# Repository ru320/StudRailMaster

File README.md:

<p align="center"><b>Drive your brick-built trains from your computer or a home-made remote –<br>via Bluetooth, without internet, without an account.</b></p>

<p align="center">🇩🇪 <a href="README.de.md">Deutsche Fassung</a> · <a href="docs/en/install.md">Installation</a> · <a href="docs/en/user-guide.md">User guide</a> · <a href="docs/en/remote-setup.md">Remote</a></p>

---

## Why?

The layout runs trains with motor hubs from three makers: a cheap JMC hub, a Mould King 4.0 from the Orient Express and a LEGO City Hub from the freight train 60337. Every hub wants its own phone app. Every app has different sliders, and driving two trains at once means two phones.

I wanted **one control desk for all trains** – ideally with **real levers** you push with your thumb, and a **big red button** that really stops everything. No account, no ads, no cloud. That turned into two things:

| | |
|---|---|
| **Stud Rail Master** – the PC program | for Windows, macOS and Linux. Find hubs, add photos of your trains, assign levers, drive. Needs no extra hardware. |
| **Stud Rail Master Quadro** – the remote | an ESP32 with four slide pots, direction switches and an emergency stop. Drives up to four hubs on its own, no PC needed; set up through a web page in your phone's browser. |

Both share the same drivers and take turns: when the PC starts it takes over the radio, when it quits the remote drives again.

## What it looks like

Every socket of every hub gets a throttle – spread any way you like: two motors on one throttle, one throttle across several hubs (even from different makers), single motors inverted. More in the [user guide](docs/en/user-guide.md#the-idea-throttles-and-hubs).

- **One lever per throttle** – drag up to go faster, one tap to change direction, a big red emergency stop (also on the space bar).
- **Your trains, your pictures** – put a photo on every hub so you always know which lever moves which train.
- **Many trains at once** – up to 16 throttles; one throttle can drive several locomotives, even from different makers.
- **Gentle direction changes** – the train slows down and starts off the other way, instead of jerking.
- **Stays at home** – no internet, no account, no advertising, no data collection.
- **Help built in** – the same guide as here, offline in the program (the **?** button).

## Which hubs?

| Hub | Windows | macOS | Linux | Remote |
|---|:-:|:-:|:-:|:-:|
| **JMC hub** (shows up as “JG_JMC-…”, ports A–D) | ✔ | ✔ | ✔ | ✔ |
| **Mould King 4.0** (ports A–D, up to 3 hubs) | ⚠ not yet tested | ✘ → Linux or ESP32 with web page | ✔ one-time unlock | ✔ |
| **LEGO Powered Up City Hub** (88009, e.g. set 60337, ports A/B) | ✔ | ✔ | ✔ | ✔ |

**Planned:**
- **IR hubs** (infrared, protocol like LEGO Power Functions) – transmitter in the remote, the window in the case is already there
- **BlueBrixx hubs with 2.4 GHz radio**
- **LEGO Technic Hub** (4 ports), **Mould King 6.0** (as soon as the hubs are available)

## Get started

1. Download the program for your system from the **releases** page and unpack it.
2. Start it, switch your hub on, find it under *Settings → Find hubs*, assign a throttle – and off you go.

Step by step: **[Installation](docs/en/install.md)** · **[User guide](docs/en/user-guide.md)** · **[Set up the remote](docs/en/remote-setup.md)** · **[Together with the remote](docs/en/esp-sync.md)**

Want to try it without a hub first? **Demo mode** simulates three trains (see the user guide).

<details>
<summary><b>Or run it from source</b></summary>

With Python 3.10 or newer: download or clone this repository, then start `app/start.sh` (Linux), `app/start.command` (macOS) or `app/start.bat` (Windows). The first start sets everything up and downloads the required Python packages once; after that it starts right away.
</details>

## Safety

Some hubs simply keep running their last command when they hear nothing more. So everywhere:

- **Emergency stop** halts every train immediately – even in the middle of a direction change.
- **Nothing moves until every lever has been at 0** – after switching on and after every emergency stop.
- **On quit, on a lost connection and before every restart** a stop is sent actively.
- When you drive through the remote's web page, it triggers an emergency stop as soon as the page has been silent for 2 seconds.

## The long road

No maker has published its protocol (except LEGO). What now fits into a few lines of driver cost quite a few evenings:

<details>
<summary><b>JMC: the hub that would not listen</b></summary>

The protocol comes from a capture of the original app: 11 bytes, a checksum, done – or so I thought. The hub still ignored every drive command. The reason: a freshly switched-on hub has to receive a **stop** first, before it moves at all. Then came the second surprise: it has **no watchdog**. If the connection drops, the motor just keeps running – more than 20 seconds in the test, until it was switched off. Since then every path out of the program actively sends stop. And because ports A+B share one speed byte, two motors stuttered as soon as you tried to drive them separately.
</details>

<details>
<summary><b>Mould King 4.0: radio without a connection</b></summary>

This hub never connects. It is controlled through encrypted **Bluetooth advertising packets** that the app sends every 100 ms with a changing address. The encryption could be rebuilt thanks to other people's work (see [THIRD_PARTY.md](THIRD_PARTY.md)) – and still nothing moved. In broadcast mode Linux drops three inconspicuous bytes (the “flags” `02 01 02`), and **without exactly those three bytes the hub ignores everything**. On Linux the commands now go straight to the Bluetooth chip. macOS doesn't allow that at all. By the way: one reference had forward and reverse swapped.
</details>

<details>
<summary><b>LEGO City Hub: the impatient one</b></summary>

The only hub with open documentation – and still fussy: if nobody connects right away, it **switches itself off after a few seconds**. So the program no longer searches at leisure but grabs it the moment it shows up.
</details>

<details>
<summary><b>Packaging: 301 MB for one window</b></summary>

The first Linux program accidentally bundled the whole GTK toolkit and weighed **301 MB** – and still didn't run everywhere, because WebKitGTK can't be packed portably. Now it ships Qt WebEngine (171 MB). The built-in Chromium sandbox failed on locked-down namespaces, an AppImage can't be given special privileges, and the Mould King radio needs exactly such a privilege – so there is now a tiny helper you unlock once with your password. And for a while, the browser opened every time along with the program window.
</details>

New findings about hubs go into `drivers/*.json` as test vectors – so PC and remote check on every build that they still send exactly the same bytes.

## The remote

An ESP32 DevKit, four 75 mm slide pots, four toggle switches with an LED for the direction, an emergency-stop button and 4× AA batteries in a printed case. The firmware also works on its own without any of that – then the levers are sliders on the web page `StudRailMasterQuadro.local`.

> **Preview – not yet printed or tested.** The case is fully designed on the computer but nobody has built it yet. If you print it first, feedback is welcome.

- **[Case](hardware/gehaeuse/README.md)** (German) – 180 × 180 mm desk, every part printable in one colour (build plate from 185 × 185 mm), STL files and a parametric CAD model (SolidCraft, STEP)
- **[Parts list](hardware/BOM.md)** (German) – electronics, bought parts, screws
- **[Flash and set up the firmware](docs/en/remote-setup.md)** – already works with a bare ESP32 DevKit
- Schematic to follow; the pin assignment is in the parts list.

## For developers

The project consists of the PC program (`app/`, Python) and the firmware of the ESP32 remote (`src/`, `lib/`, PlatformIO). Both share the same hub drivers (`drivers/`).

- [Drivers: shared between ESP32 and PC](docs/en/dev/drivers.md)
- [Building, testing, internals](docs/en/dev/building.md)

## License

Free software and open hardware – if you change it and pass it on, you must share it under the same terms:

| Part | License |
|---|---|
| Software (`app/`, `src/`, `lib/`, `test/`, `tools/`, `drivers/`) | [GPL-3.0-or-later](LICENSE) |
| Hardware (`hardware/`: schematic, PCB, enclosure) | [CERN-OHL-S-2.0](LICENSES/CERN-OHL-S-2.0.txt) |
| Docs, images, logo (`docs/`, `README*`) | [CC BY-SA 4.0](LICENSES/CC-BY-SA-4.0.txt) |

Third-party parts (Barlow fonts, prior work on Mould King) and their licenses: [THIRD_PARTY.md](THIRD_PARTY.md).

LEGO® is a trademark of the LEGO Group, Mould King a trademark of its manufacturer. This project is not sponsored or endorsed by either; the names only describe which hubs it works with.

---

<p align="center"><i>In Herbrechtingen ist es immer am schönsten!</i></p>

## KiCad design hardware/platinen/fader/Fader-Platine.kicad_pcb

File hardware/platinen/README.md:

# Platinen Handgerät „Stud Rail Master Quadro“

> **Entwurf, ungetestet.** Beide Platinen sind platziert und gegen das Gehäuse geprüft, aber noch nicht gefertigt. Vor der Bestellung die Punkte unter [Vor der Bestellung prüfen](#vor-der-bestellung-prüfen) abhaken.

Zwei Platinen, 2 Lagen, 1,6 mm FR4, Masse auf beiden Seiten als Fläche:

| Platine | Größe | Inhalt |
|---|---|---|
| [Fader-Platine](fader/) | 91 × 91 mm | 4 Schiebepotis B103 75 mm, je 1 k + 100 nF am Schleifer, Stecker zur Hauptplatine |
| [Hauptplatine](hauptplatine/) | 100 × 52 mm | ESP32-DevKit V1 (30 Pin, kopfüber darunter), MT3608-Modul (unten), 1N5819, Batteriemessung, IR-Treiber, LED-Widerstände, Stecker für alles am Gehäuse, Anschluss für ein 2,4-GHz-Funkmodul |

Je Platine liegen Schaltplan (`.kicad_sch`), Platine (`.kicad_pcb`) und Projekt (`.kicad_pro`) im Ordner. Eigene Footprints (Fader, MT3608-Modul) stehen in [`ZugFern.pretty/`](ZugFern.pretty/).

## Im Gehäuse

- **Fader-Platine:** Sie sitzt auf den 4 Säulen unter der Frontplatte (4 × M3 × 6 in Gewindeeinsätze). Die Fader drücken mit ihrer Oberseite gegen die Frontplatte. Der Stecker J1 sitzt **unten** auf der Platine.
- **Hauptplatine:** Sie liegt waagrecht im linken hinteren Teil der Unterschale, 12,4 mm über dem Boden, auf 4 eigenen Säulen (4 × M3 × 6 von oben).
  - Das ESP32-DevKit hängt kopfüber darunter: Seine Stiftleisten stecken von unten durch die Platine und werden oben verlötet. Die Platine liegt dabei auf dem Kunststoff der Stiftleisten auf.
  - Die Micro-USB-Buchse zeigt nach vorn auf das Langloch in der Stirnwand.
  - Über der WLAN/BLE-Antenne des ESP32 ist die Platine ausgespart.
  - Das MT3608-Modul hängt an 4 Drahtbeinchen (abgeschnittene Bauteilbeine) etwa 2 mm unter der Platine, Bauteilseite nach unten.

## Stecker (JST XH, 2,5 mm)

| Stecker | Pins | Wohin |
|---|---|---|
| J1 (Fader-Platine) ↔ J4 (Hauptplatine) | 1 +3V3, 2 GND, 3–6 Regler 1–4 | Kabel 1:1, 6-polig |
| J3 | 1 VSYS, 2 GND | 4 × AA über den Ein/Aus-Schalter an der linken Wand |
| J5–J8 | 1 Schalter, 2 LED-Anode, 3 GND | Regler 1–4: Kippschalter (Mitte → Pin 1, ein Außenanschluss → GND) und Richtungs-LED |
| J9 | 1 Not-Stopp, 2 GND | Cherry-MX-Schalter |
| J10 | 1 Status-LED, 2 Batterie-LED, 3 GND | die beiden 3-mm-LEDs neben dem Not-Stopp (Anoden an 1/2) |
| J11 | 1–4 Anoden IR1–IR4, 5 gemeinsame Kathode | IR-LEDs im IR-Block (IR1 = TSAL6100 Mitte, IR2/IR3 = TSAL6200 ±30°, IR4 = TSAL6200 45° nach oben) |
| J12 | wie nRF24L01+ (1 GND, 2 3V3, 3 CE, 4 CSN, 5 SCK, 6 MOSI, 7 MISO, 8 IRQ) | Funkmodul nRF24L01+ im Funk-Halter unter dem Not-Stopp, 8 Dupont-Kabel Buchse–Buchse |

## Kabel

Vorschlag für Farben und Querschnitte (so sind die Kabel auch im CAD-Modell gezogen):

| Farbe | Wofür | Querschnitt |
|---|---|---|
| rot | Plus: Batterie, VSYS, +3V3 zur Fader-Platine | 0,25 mm² (AWG 24) für Batterie/VSYS, sonst 0,14 mm² |
| schwarz | GND, gemeinsame Kathode der IR-LEDs | 0,25 mm² für Batterie und IR-Kathode, sonst 0,14 mm² |
| gelb | Regler (Fader-Kabel) und Kippschalter | 0,14 mm² (AWG 26) |
| grün | LED-Anoden (Richtung, Status, Batterie) | 0,14 mm² |
| blau | Not-Stopp, IR-Anoden | 0,14 mm² |

- Die Kathoden der Richtungs-LEDs bekommen eine kurze schwarze Brücke zum GND-Anschluss des Kippschalters.
- Die IR-Kathoden sind als Kette verbunden, ebenso die Kathoden der Status- und der Batterie-LED.
- JST-XH-Crimpkontakte nehmen AWG 22–28.

## Pinbelegung ESP32

Wie in `src/Pins.h`, dazu neu:

| Funktion | GPIO |
|---|---|
| Batterie-LED | 12 (LED mit 330 Ω gegen GND hält den Strapping-Pin beim Booten auf LOW, wie er sein muss) |
| 2,4-GHz-Modul: SCK, MOSI, MISO, CSN, CE, IRQ | 14, 13, 39, 5, 4, 15 |
| Batteriespannung (VSYS × 0,405) | 36 |
| IR-Sender | 26 |

Für die Batterie-LED, die Batteriemessung, den IR-Sender und das Funkmodul fehlt die Firmware noch.

## Bestückung

Nur Durchsteckmontage, keine SMD-Teile: Widerstände 0207 liegend, Keramik-Scheibenkondensatoren RM 2,5, Elko radial, 1N5819 (DO-41), BC337 (TO-92) als IR-Treiber.

1. **MT3608 vorher einstellen:** an 5 V Labornetzteil oder 4 × AA, Poti drehen bis 5,0 V am Ausgang.
2. Hauptplatine: zuerst die flachen Teile (Widerstände, Diode, Kondensatoren, BC337), dann Elko C1 (Ø 8 mm, max. 12 mm hoch), JST-Stecker und J12. Die Beinchen von J5 und D1 liegen über dem DevKit: auf 1 mm kürzen.
3. MT3608 mit 4 Drahtbeinchen unten anlöten (Bauteilseite nach unten, ca. 2 mm Abstand).
4. ESP32-DevKit von unten einstecken, Platine plan auf die Stiftleisten drücken, oben verlöten. Danach lässt sich das DevKit nur noch mit Entlötlitze tauschen.
5. Fader-Platine: R und C, dann die Fader. Die Haltelaschen durch die Löcher stecken, verdrehen und verlöten. J1 auf die Unterseite.

## Vor der Bestellung prüfen

- [ ] **Fader:** Die Platine auf 1:1 ausdrucken (KiCad: Drucken, Maßstab 1) und einen Fader auflegen. Das Pinbild stammt aus dem Datenblatt (Raster 2,5 mm, Enden 70 mm auseinander). Das 3D-Modell eines anderen Herstellers hatte 2,7 mm und 73,2 mm. Liegen die Pins anders, `Fader_B103_75mm_Dual` in `tools/gen_platinen.py` anpassen.
- [ ] **0 % am richtigen Ende:** Pin 3 (GND) liegt am Nutzer-Ende. Zeigt der Regler verkehrt herum an, Pin 1 und 3 tauschen.
- [ ] **ESP32-DevKit:** Die Pinfolge mit dem eigenen Board vergleichen. Es gibt 30-Pin-Varianten mit anderer Reihenfolge. Die Reihen liegen 25,4 mm auseinander.
- [ ] **MT3608-Modul:** Die Lage der 4 Anschlüsse am eigenen Modul messen. Die Langlöcher gleichen ± 1 mm aus.
- [ ] **Säulen und Langloch:** Erst die Unterschale drucken und die bestückte Hauptplatine mit ESP probehalber einsetzen.

## Bearbeiten

Die Dateien lassen sich direkt in KiCad 10 öffnen (`.kicad_pro`). Werden Lage oder Umriss der Platinen geändert, müssen Säulen und Aussparungen im Gehäuse mitziehen ([gehaeuse/](../gehaeuse/README.md)).

*In Herbrechtingen ist es immer am schönsten!*

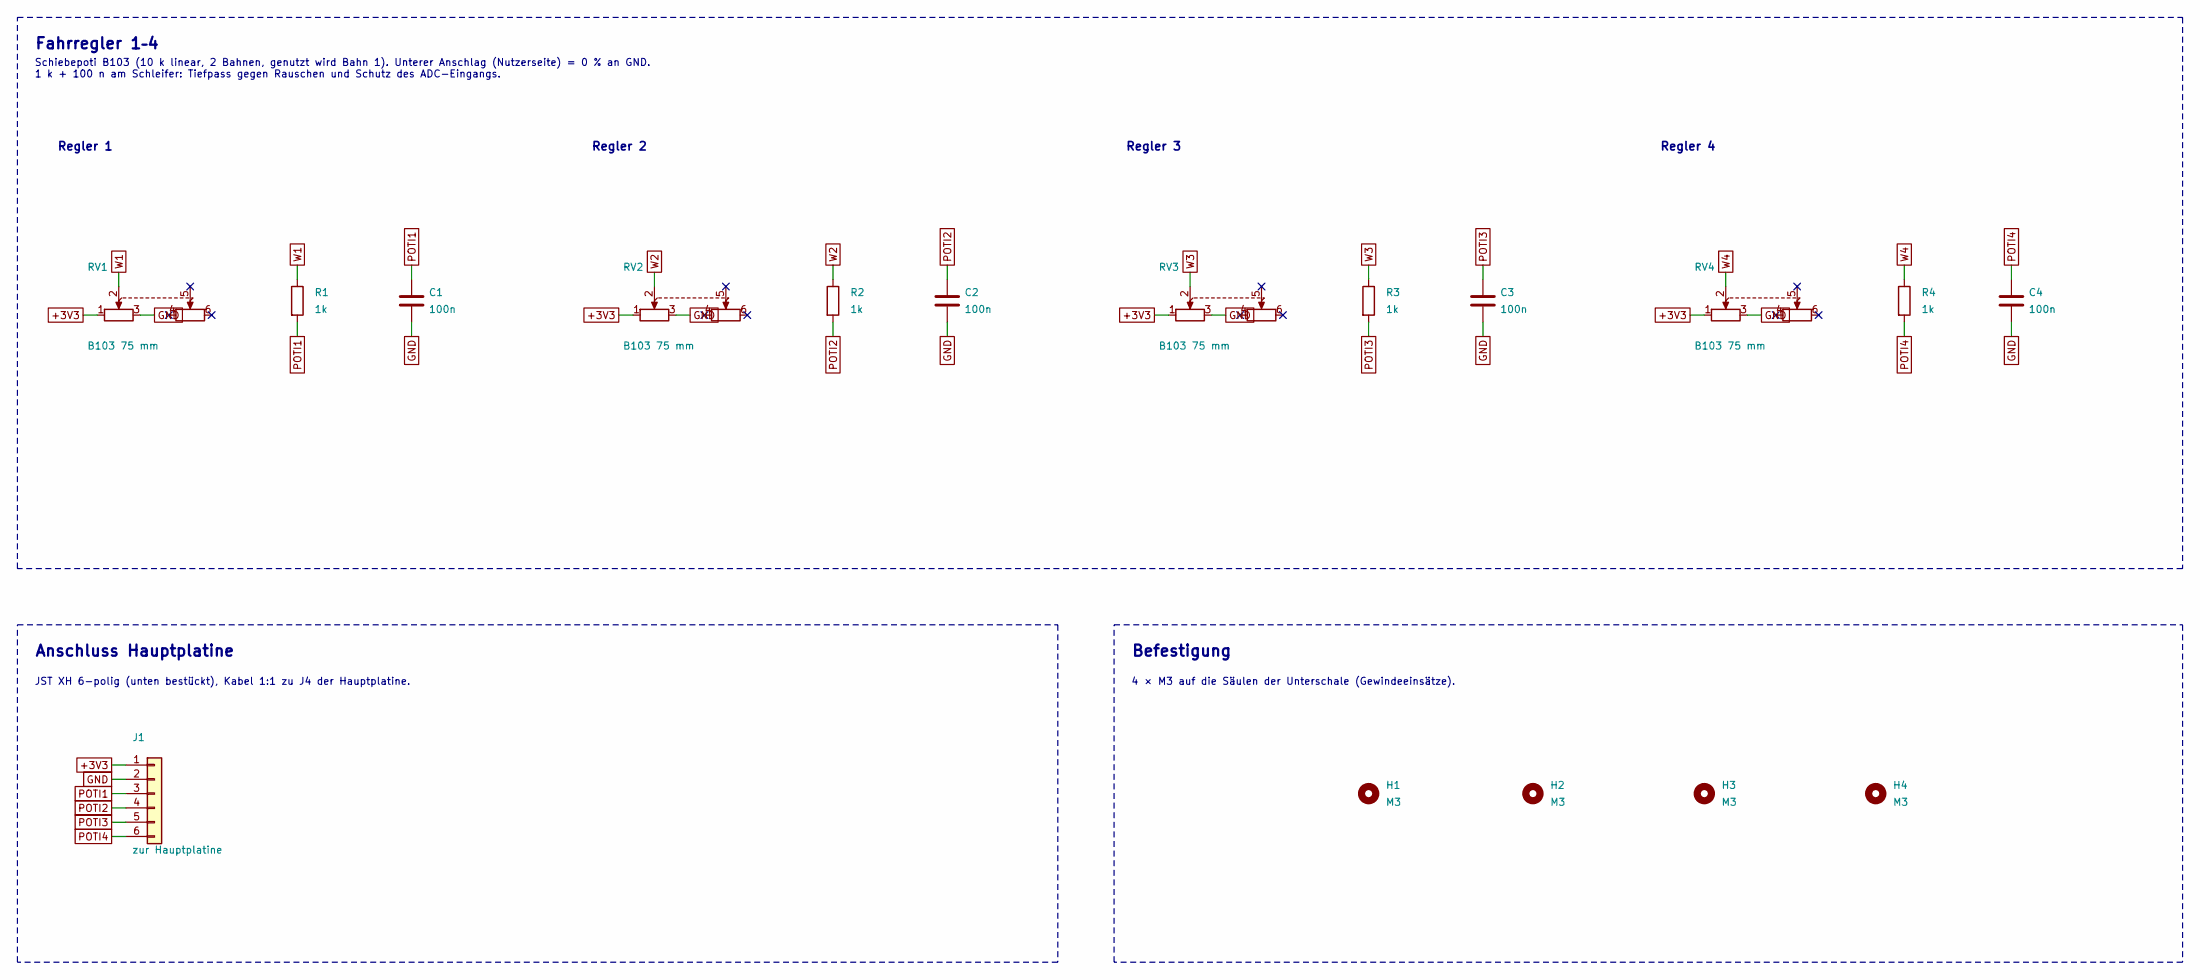
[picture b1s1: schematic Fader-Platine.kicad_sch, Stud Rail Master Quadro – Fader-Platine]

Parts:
C1, C2, C3, C4: 100n; C_Disc_D3.0mm_W1.6mm_P2.50mm
H1, H2, H3, H4: M3; MountingHole_3.2mm_M3
J1: zur Hauptplatine; JST_XH_B6B-XH-A_1x06_P2.50mm_Vertical
R1, R2, R3, R4: 1k; R_Axial_DIN0207_L6.3mm_D2.5mm_P7.62mm_Horizontal
RV1, RV2, RV3, RV4: B103 75 mm; Fader_B103_75mm_Dual

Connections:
+3V3: J1.1, RV1.1, RV2.1, RV3.1, RV4.1
GND: C1.2, C2.2, C3.2, C4.2, J1.2, RV1.3, RV2.3, RV3.3, RV4.3
POTI1: C1.1, J1.3, R1.2
POTI2: C2.1, J1.4, R2.2
POTI3: C3.1, J1.5, R3.2
POTI4: C4.1, J1.6, R4.2
W1: R1.1, RV1.2
W2: R2.1, RV2.2
W3: R3.1, RV3.2
W4: R4.1, RV4.2

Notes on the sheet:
Fahrregler 1–4
Schiebepoti B103 (10 k linear, 2 Bahnen, genutzt wird Bahn 1). Unterer Anschlag (Nutzerseite) = 0 % an GND. 1 k + 100 n am Schleifer: Tiefpass gegen Rauschen und Schutz des ADC-Eingangs.
Regler 1
Regler 2
Regler 3
Regler 4
Anschluss Hauptplatine
JST XH 6-polig (unten bestückt), Kabel 1:1 zu J4 der Hauptplatine.
Befestigung
4 × M3 auf die Säulen der Unterschale (Gewindeeinsätze).

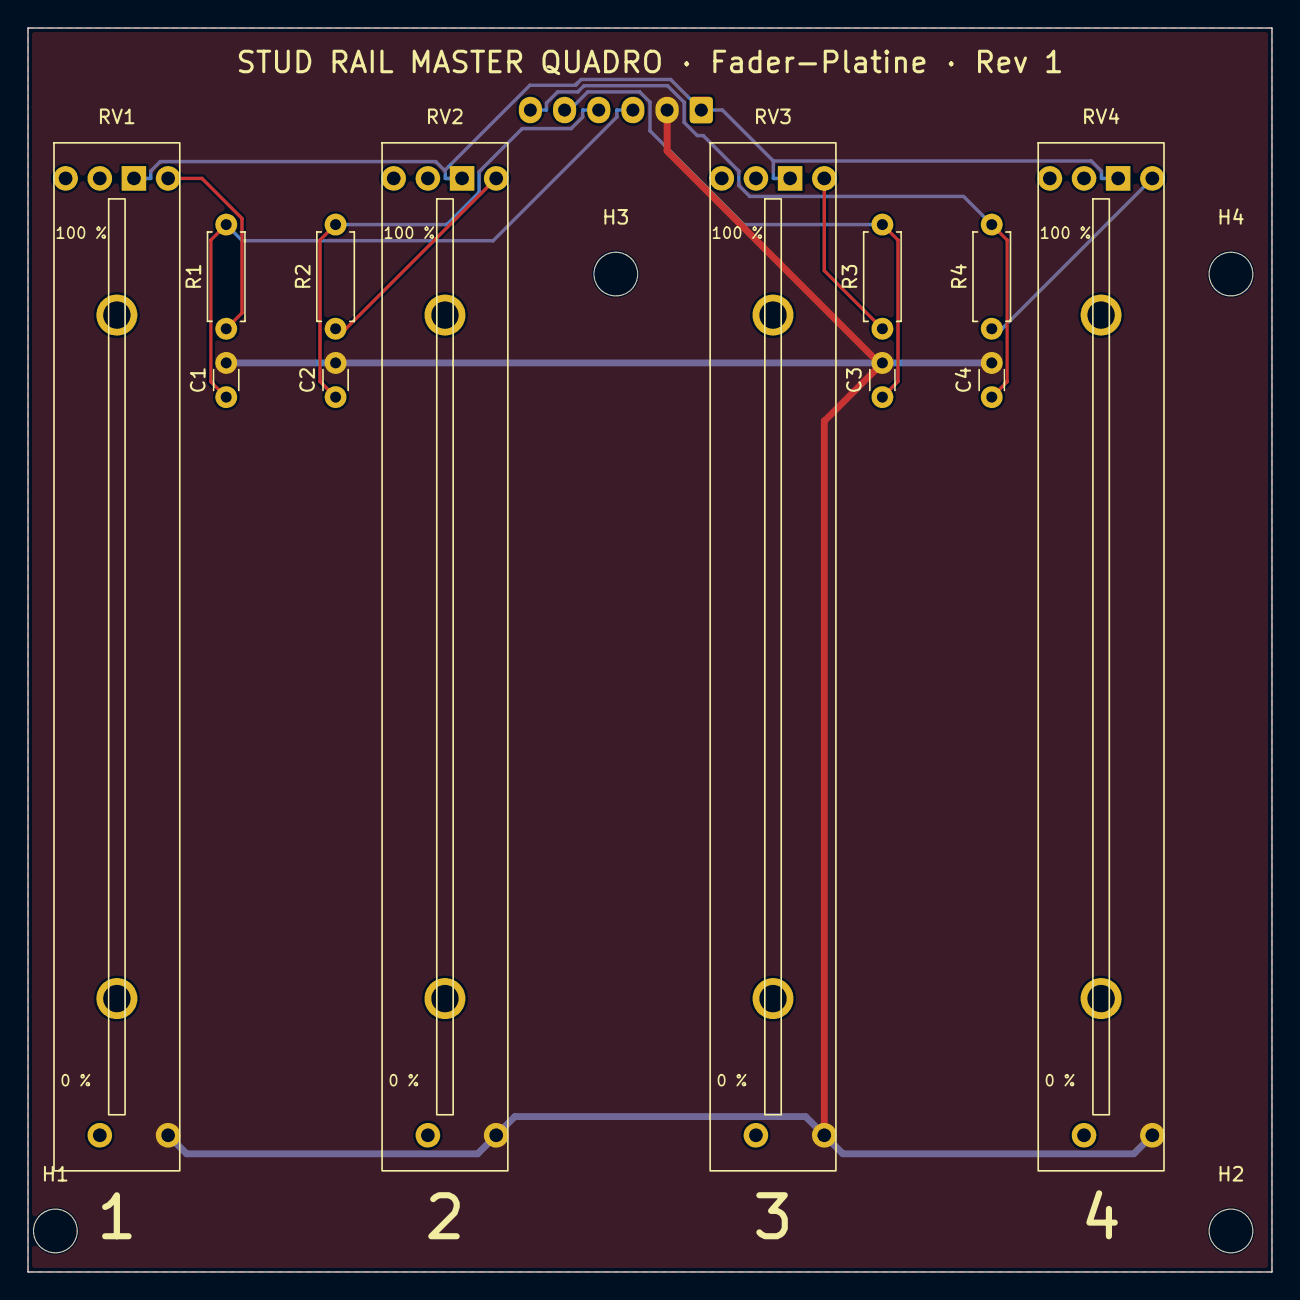
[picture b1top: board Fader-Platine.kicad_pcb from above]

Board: 2 copper layers, 91.0 x 91.0 mm, 17 parts (1 on the bottom side), 10 nets.

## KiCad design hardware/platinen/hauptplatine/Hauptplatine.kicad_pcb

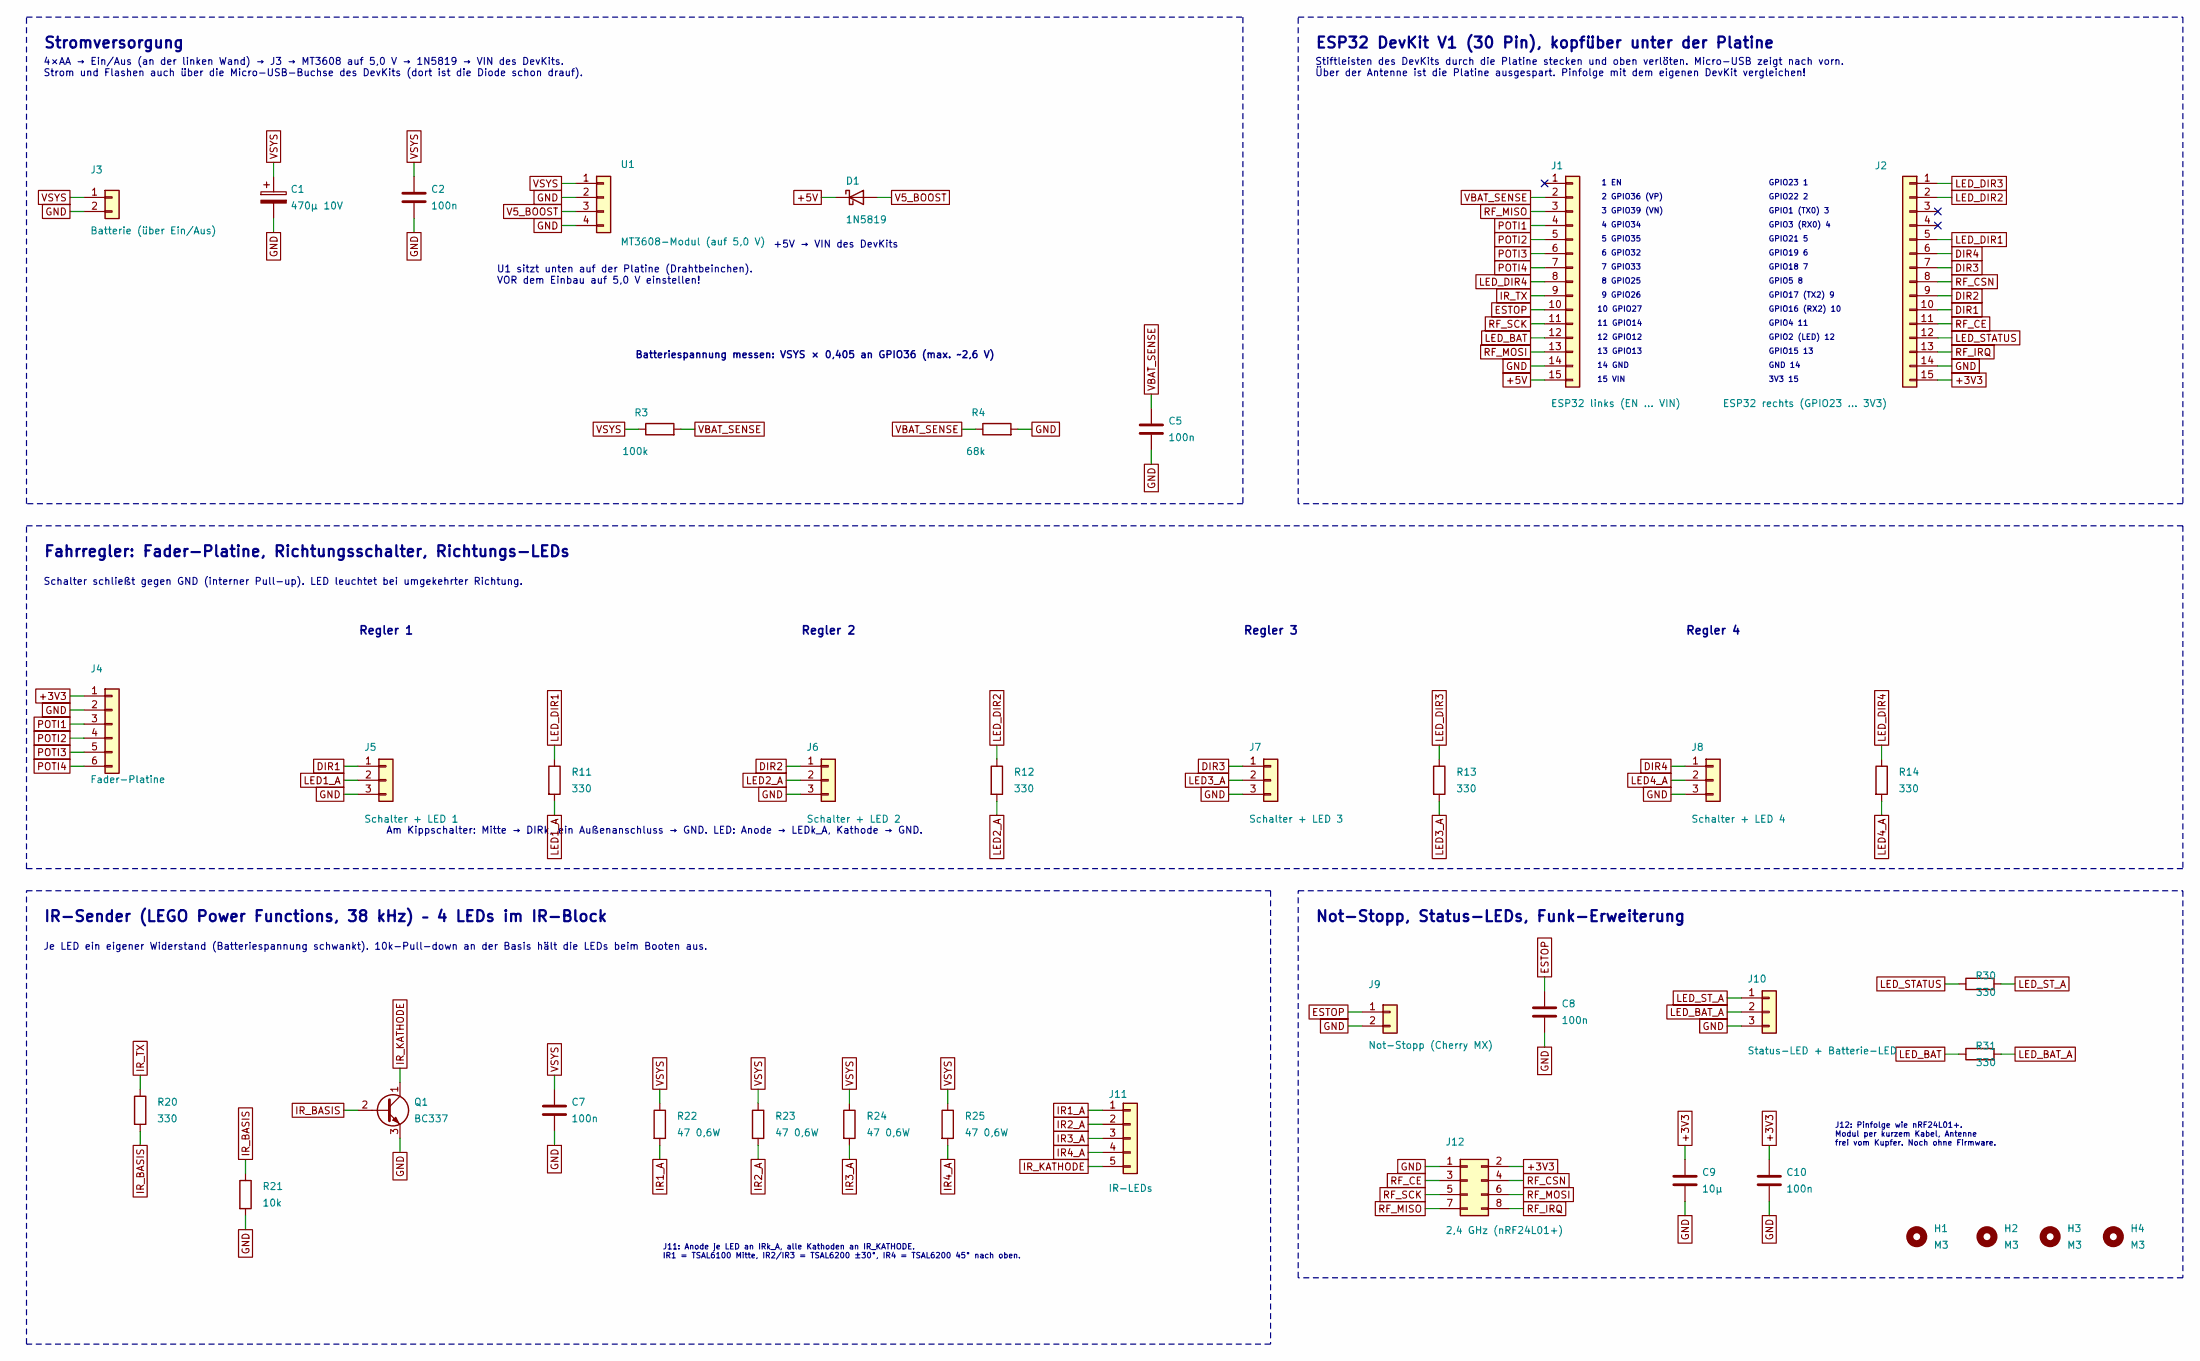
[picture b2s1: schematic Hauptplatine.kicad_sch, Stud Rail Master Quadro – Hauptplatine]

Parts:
C1: 470µ 10V; CP_Radial_D8.0mm_P3.50mm
C2, C5, C7, C8, C10: 100n; C_Disc_D3.0mm_W1.6mm_P2.50mm
C9: 10µ; C_Disc_D3.0mm_W2.0mm_P2.50mm
D1: 1N5819; D_DO-41_SOD81_P10.16mm_Horizontal
H1, H2, H3, H4: M3; MountingHole_3.2mm_M3
J1: ESP32 links (EN … VIN); PinHeader_1x15_P2.54mm_Vertical
J2: ESP32 rechts (GPIO23 … 3V3); PinHeader_1x15_P2.54mm_Vertical
J3: Batterie (über Ein/Aus); JST_XH_B2B-XH-A_1x02_P2.50mm_Vertical
J4: Fader-Platine; JST_XH_B6B-XH-A_1x06_P2.50mm_Vertical
J5: Schalter + LED 1; JST_XH_B3B-XH-A_1x03_P2.50mm_Vertical
J6: Schalter + LED 2; JST_XH_B3B-XH-A_1x03_P2.50mm_Vertical
J7: Schalter + LED 3; JST_XH_B3B-XH-A_1x03_P2.50mm_Vertical
J8: Schalter + LED 4; JST_XH_B3B-XH-A_1x03_P2.50mm_Vertical
J9: Not-Stopp (Cherry MX); JST_XH_B2B-XH-A_1x02_P2.50mm_Vertical
J10: Status-LED + Batterie-LED; JST_XH_B3B-XH-A_1x03_P2.50mm_Vertical
J11: IR-LEDs; JST_XH_B5B-XH-A_1x05_P2.50mm_Vertical
J12: 2,4 GHz (nRF24L01+); PinHeader_2x04_P2.54mm_Vertical
Q1: BC337; TO-92_Inline
R3: 100k; R_Axial_DIN0207_L6.3mm_D2.5mm_P7.62mm_Horizontal
R4: 68k; R_Axial_DIN0207_L6.3mm_D2.5mm_P7.62mm_Horizontal
R11, R12, R13, R14, R20: 330; R_Axial_DIN0207_L6.3mm_D2.5mm_P7.62mm_Horizontal
R21: 10k; R_Axial_DIN0207_L6.3mm_D2.5mm_P7.62mm_Horizontal
R22, R23, R24, R25: 47 0,6W; R_Axial_DIN0207_L6.3mm_D2.5mm_P10.16mm_Horizontal
R30, R31: 330; R_Axial_DIN0207_L6.3mm_D2.5mm_P2.54mm_Vertical
U1: MT3608-Modul (auf 5,0 V); MT3608_Modul

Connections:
+3V3: C9.1, C10.1, J2.15, J4.1, J12.2
+5V: D1.1 (K), J1.15
DIR1: J2.10, J5.1
DIR2: J2.9, J6.1
DIR3: J2.7, J7.1
DIR4: J2.6, J8.1
ESTOP: C8.1, J1.10, J9.1
GND: C1.2, C2.2, C5.2, C7.2, C8.2, C9.2, C10.2, J1.14, J2.14, J3.2, J4.2, J5.3, J6.3, J7.3, J8.3, J9.2, J10.3, J12.1, Q1.3 (E), R4.2, R21.2, U1.2, U1.4
IR1_A: J11.1, R22.2
IR2_A: J11.2, R23.2
IR3_A: J11.3, R24.2
IR4_A: J11.4, R25.2
IR_BASIS: Q1.2 (B), R20.2, R21.1
IR_KATHODE: J11.5, Q1.1 (C)
IR_TX: J1.9, R20.1
LED1_A: J5.2, R11.2
LED2_A: J6.2, R12.2
LED3_A: J7.2, R13.2
LED4_A: J8.2, R14.2
LED_BAT: J1.12, R31.1
LED_BAT_A: J10.2, R31.2
LED_DIR1: J2.5, R11.1
LED_DIR2: J2.2, R12.1
LED_DIR3: J2.1, R13.1
LED_DIR4: J1.8, R14.1
LED_STATUS: J2.12, R30.1
LED_ST_A: J10.1, R30.2
POTI1: J1.4, J4.3
POTI2: J1.5, J4.4
POTI3: J1.6, J4.5
POTI4: J1.7, J4.6
RF_CE: J2.11, J12.3
RF_CSN: J2.8, J12.4
RF_IRQ: J2.13, J12.8
RF_MISO: J1.3, J12.7
RF_MOSI: J1.13, J12.6
RF_SCK: J1.11, J12.5
V5_BOOST: D1.2 (A), U1.3
VBAT_SENSE: C5.1, J1.2, R3.2, R4.1
VSYS: C1.1, C2.1, C7.1, J3.1, R3.1, R22.1, R23.1, R24.1, R25.1, U1.1

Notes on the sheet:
Stromversorgung
4×AA → Ein/Aus (an der linken Wand) → J3 → MT3608 auf 5,0 V → 1N5819 → VIN des DevKits. Strom und Flashen auch über die Micro-USB-Buchse des DevKits (dort ist die Diode schon drauf).
U1 sitzt unten auf der Platine (Drahtbeinchen). VOR dem Einbau auf 5,0 V einstellen!
+5V → VIN des DevKits
Batteriespannung messen: VSYS × 0,405 an GPIO36 (max. ~2,6 V)
ESP32 DevKit V1 (30 Pin), kopfüber unter der Platine
Stiftleisten des DevKits durch die Platine stecken und oben verlöten. Micro-USB zeigt nach vorn. Über der Antenne ist die Platine ausgespart. Pinfolge mit dem eigenen DevKit vergleichen!
1 EN
GPIO23 1
2 GPIO36 (VP)
GPIO22 2
3 GPIO39 (VN)
GPIO1 (TX0) 3
4 GPIO34
GPIO3 (RX0) 4
5 GPIO35
GPIO21 5
6 GPIO32
GPIO19 6
7 GPIO33
GPIO18 7
8 GPIO25
GPIO5 8
9 GPIO26
GPIO17 (TX2) 9
10 GPIO27
GPIO16 (RX2) 10
11 GPIO14
GPIO4 11
12 GPIO12
GPIO2 (LED) 12
13 GPIO13
GPIO15 13
14 GND
GND 14
15 VIN
3V3 15
Fahrregler: Fader-Platine, Richtungsschalter, Richtungs-LEDs
Schalter schließt gegen GND (interner Pull-up). LED leuchtet bei umgekehrter Richtung.
Regler 1

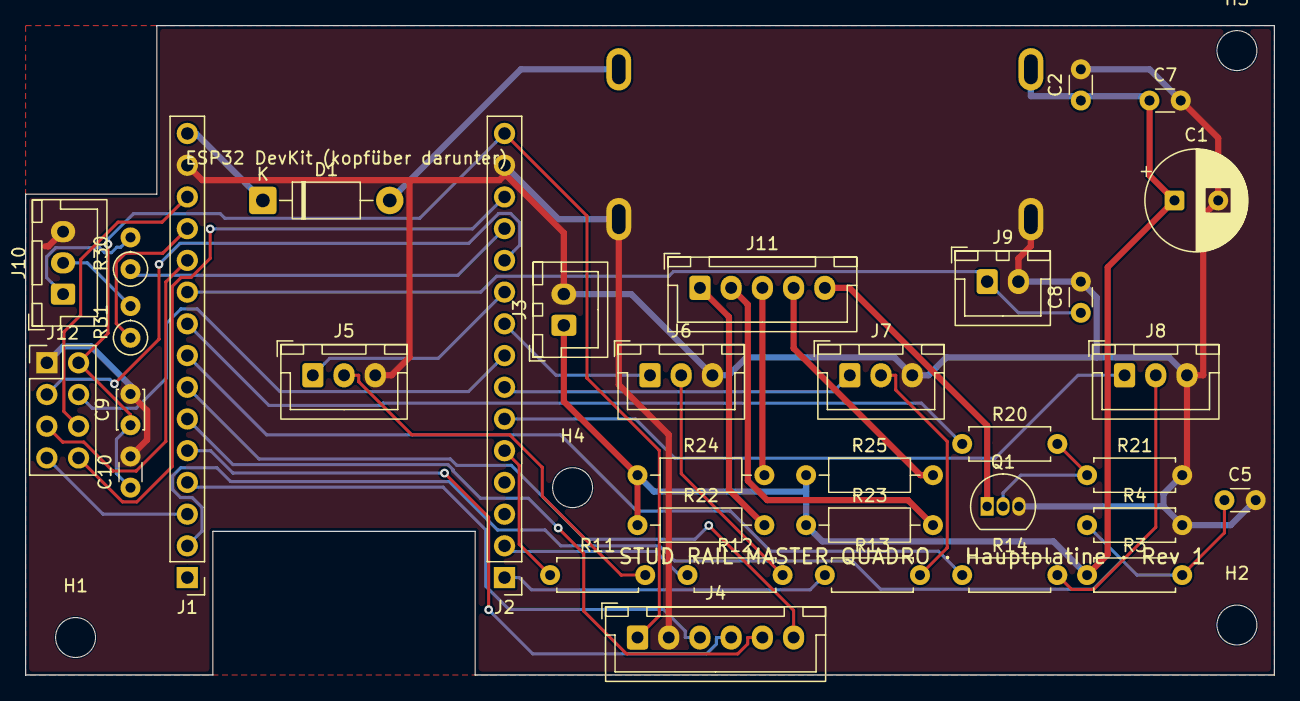
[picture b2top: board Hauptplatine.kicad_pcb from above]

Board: 2 copper layers, 100.0 x 52.0 mm, 40 parts (1 on the bottom side), 40 nets.

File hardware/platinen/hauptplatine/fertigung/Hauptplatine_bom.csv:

Comment,Designator,Footprint,Quantity
470µ 10V,C1,CP_Radial_D8.0mm_P3.50mm,1
100n,"C2,C5,C7,C8,C10",C_Disc_D3.0mm_W1.6mm_P2.50mm,5
10µ,C9,C_Disc_D3.0mm_W2.0mm_P2.50mm,1
1N5819,D1,D_DO-41_SOD81_P10.16mm_Horizontal,1
2-polig,"J3,J9",JST_XH_B2B-XH-A_1x02_P2.50mm_Vertical,2
6-polig,J4,JST_XH_B6B-XH-A_1x06_P2.50mm_Vertical,1
3-polig,"J5,J6,J7,J8,J10",JST_XH_B3B-XH-A_1x03_P2.50mm_Vertical,5
5-polig,J11,JST_XH_B5B-XH-A_1x05_P2.50mm_Vertical,1
"2,4 GHz (nRF24L01+)",J12,PinHeader_2x04_P2.54mm_Vertical,1
BC337,Q1,TO-92_Inline,1
100k,R3,R_Axial_DIN0207_L6.3mm_D2.5mm_P7.62mm_Horizontal,1
68k,R4,R_Axial_DIN0207_L6.3mm_D2.5mm_P7.62mm_Horizontal,1
330,"R11,R12,R13,R14,R20",R_Axial_DIN0207_L6.3mm_D2.5mm_P7.62mm_Horizontal,5
10k,R21,R_Axial_DIN0207_L6.3mm_D2.5mm_P7.62mm_Horizontal,1
"47 0,6W","R22,R23,R24,R25",R_Axial_DIN0207_L6.3mm_D2.5mm_P10.16mm_Horizontal,4
330,"R30,R31",R_Axial_DIN0207_L6.3mm_D2.5mm_P2.54mm_Vertical,2
"MT3608-Modul (auf 5,0 V)",U1,MT3608_Modul,1
